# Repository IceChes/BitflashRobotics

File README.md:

# What is this project?
Bitflash Robotics is an attempt to modernize combat robotics electronics. 

## Devices (see devices page for more information)
### Firefly

ESP32C3-based BLE combat robot receiver. Connects to a standard BLE game controller and controls all other robotic components. Also runs more complex compute loads if needed.

Has 2 snap (serial) ports, 1 servo port, and 1 Qwiic port. 

### Impulse

megaAVR-based brushed motor controller. Connects to one of Firefly's snap ports using a standard Qwiic/Stemma QT cable. Controls 2 brushed motors with short circuit protection and supplies 3.3v power to the robot's low voltage subsystem. 

## Standards
### BFR Packet Protocol (See Bitflash Robotics Arduino Library page for more information)

High speed structured protocol for writing sets of bytes over a standard UART bus to communicate with components. Due to its efficiency, it is able to run at extremely high speeds. Has basic error checking procedures to ensure safety and reliability in high-noise, high-intensity environments.

### Snap Serial (See Snap Serial page for more information)

Snap Serial (or just Snap) is simply UART over a Qwiic/Stemma QT port. This helps reduce connector size in the extremely tight electronics bays inside of combat robots. 

## Robots
### ???

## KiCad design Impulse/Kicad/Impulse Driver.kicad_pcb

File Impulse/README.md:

# Impulse
A better combat robot motor driver.

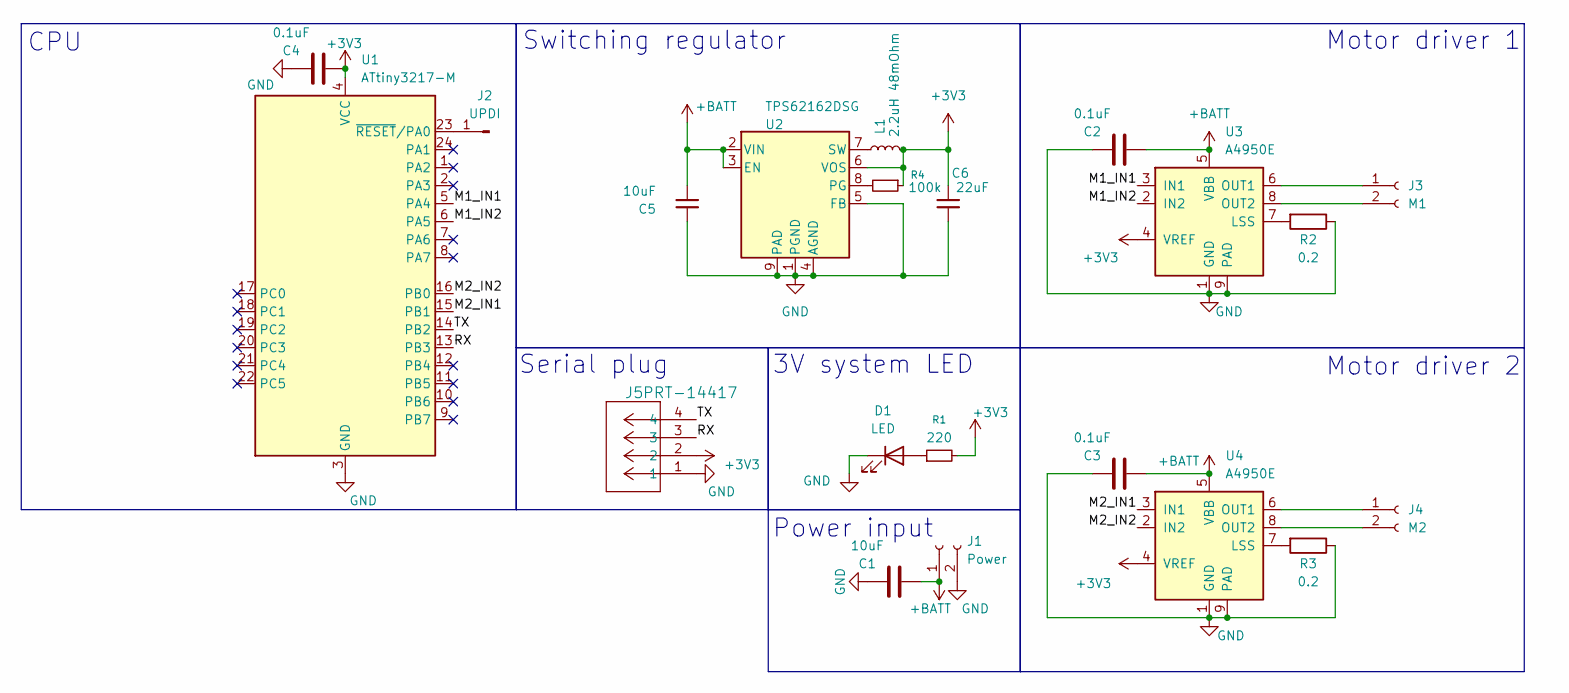
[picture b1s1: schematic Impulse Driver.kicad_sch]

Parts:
C1: 10uF; C_0805_2012Metric; LCSC C440198
C2, C3, C4: 0.1uF; C_0402_1005Metric; LCSC C14663
C5: 10uF; C_0805_2012Metric
C6: 22uF; C_0805_2012Metric
D1: LED; LED_0805_2012Metric; LCSC C965814
J1: Power; PinSocket_1x02_P2.54mm_Vertical
J2: UPDI; PinHeader_1x01_P2.54mm_Vertical
J3: M1; PinSocket_1x02_P2.54mm_Vertical
J4: M2; PinSocket_1x02_P2.54mm_Vertical
J5: PRT-14417; QWIIC_SNAPSERIAL
L1: 2.2uH 48mOhm; L_Pulse_PA4332
R1: 220; R_0402_1005Metric; LCSC C2909336
R2, R3: 0.2; R_0402_1005Metric; LCSC C7467478
R4: 100k; R_0402_1005Metric
U1: ATtiny3217-M; QFN-24-1EP_4x4mm_P0.5mm_EP2.6x2.6mm; LCSC C1340514
U2: TPS62162DSG; Texas_DSG0008A_WSON-8-1EP_2x2mm_P0.5mm_EP0.9x1.6mm_ThermalV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
U3, U4: A4950E; SOIC-8-1EP_3.9x4.9mm_P1.27mm_EP2.41x3.3mm; LCSC C82404

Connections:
+3V3: C4.1, C6.1, J5.2, L1.2, R1.2, R4.1, U1.4 (VCC), U2.6 (VOS), U3.4 (VREF), U4.4 (VREF)
+BATT: C1.1, C2.1, C3.1, C5.1, J1.1, U2.2 (VIN), U2.3 (EN), U3.5 (VBB), U4.5 (VBB)
/M1_IN1: U1.5 (PA4), U3.3 (IN1)
/M1_IN2: U1.6 (PA5), U3.2 (IN2)
/M2_IN1: U1.15 (PB1), U4.3 (IN1)
/M2_IN2: U1.16 (PB0), U4.2 (IN2)
/RX: J5.3, U1.13 (PB3)
/TX: J5.4, U1.14 (PB2)
GND: C1.2, C2.2, C3.2, C4.2, C5.2, C6.2, D1.1 (K), J1.2, J5.1, R2.1, R3.1, U1.3 (GND), U1.25 (GND), U2.1 (PGND), U2.4 (AGND), U2.5 (FB), U2.9 (PAD), U3.1 (GND), U3.9 (PAD), U4.1 (GND), U4.9 (PAD)
unnamed: D1.2 (A), R1.1
unnamed: J2.1 (Pin_1_1), U1.23 (~RESET/PA0)
unnamed: J3.1, U3.6 (OUT1)
unnamed: J3.2, U3.8 (OUT2)
unnamed: J4.1, U4.6 (OUT1)
unnamed: J4.2, U4.8 (OUT2)
unnamed: R4.2, U2.8 (PG)
unnamed: L1.1, U2.7 (SW)
unnamed: R2.2, U3.7 (LSS)
unnamed: R3.2, U4.7 (LSS)

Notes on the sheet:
Serial plug
Motor driver 2
CPU
Switching regulator
Power input
3V system LED
Motor driver 1

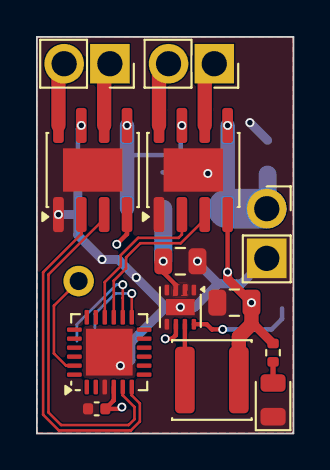
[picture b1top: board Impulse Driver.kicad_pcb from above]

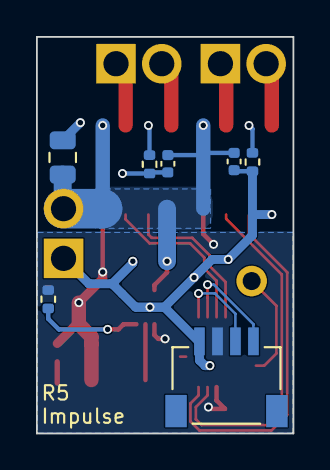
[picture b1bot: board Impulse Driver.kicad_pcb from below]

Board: 2 copper layers, 14.2 x 22.0 mm, 21 parts (7 on the bottom side), 19 nets.

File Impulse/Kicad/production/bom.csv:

Designator,Footprint,Quantity,Value,LCSC Part #
C1,0805,1,10uF,C440198
"C2, C3, C4",0402,3,0.1uF,C14663
C5,0805,1,10uF,
C6,0805,1,22uF,
D1,0805,1,LED,C965814
J1,PinSocket_1x02_P2.54mm_Vertical,1,Power,
J2,PinHeader_1x01_P2.54mm_Vertical,1,UPDI,
J5,QWIIC_SNAPSERIAL,1,PRT-14417,
L1,L_Pulse_PA4332,1,2.2uH 48mOhm,
R1,0402,1,220,C2909336
"R2, R3",0402,2,0.2,C7467478
R4,0402,1,100k,
U1,QFN-24-1EP_4x4mm_P0.5mm_EP2.6x2.6mm,1,ATtiny3217-M,C1340514
U2,Texas_DSG0008A_WSON-8-1EP_2x2mm_P0.5mm_EP0.9x1.6mm_ThermalVias,1,TPS62162DSG,
"U3, U4",SOIC-8-1EP_3.9x4.9mm_P1.27mm_EP2.41x3.3mm,2,A4950E,C82404

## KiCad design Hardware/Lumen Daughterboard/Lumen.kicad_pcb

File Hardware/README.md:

# Hardware
3D files and PCBs that aren't robots.

- JTAG2UPDI Carrier: A PCB where an Arduino Nano is used as a JTAG2UPDI programmer. Untested.
- Plastic Hub: A plastic version of a foam wheel hub for prototyping. Tested. Kinda works.
- SDMD: Atmega328P-based motor controller. Tested. Working.
- SnapSerial Driver: Attiny3217-based motor controller. Untested.
- Firefly Receiver: XIAO ESP32C3-based receiver. Untested.

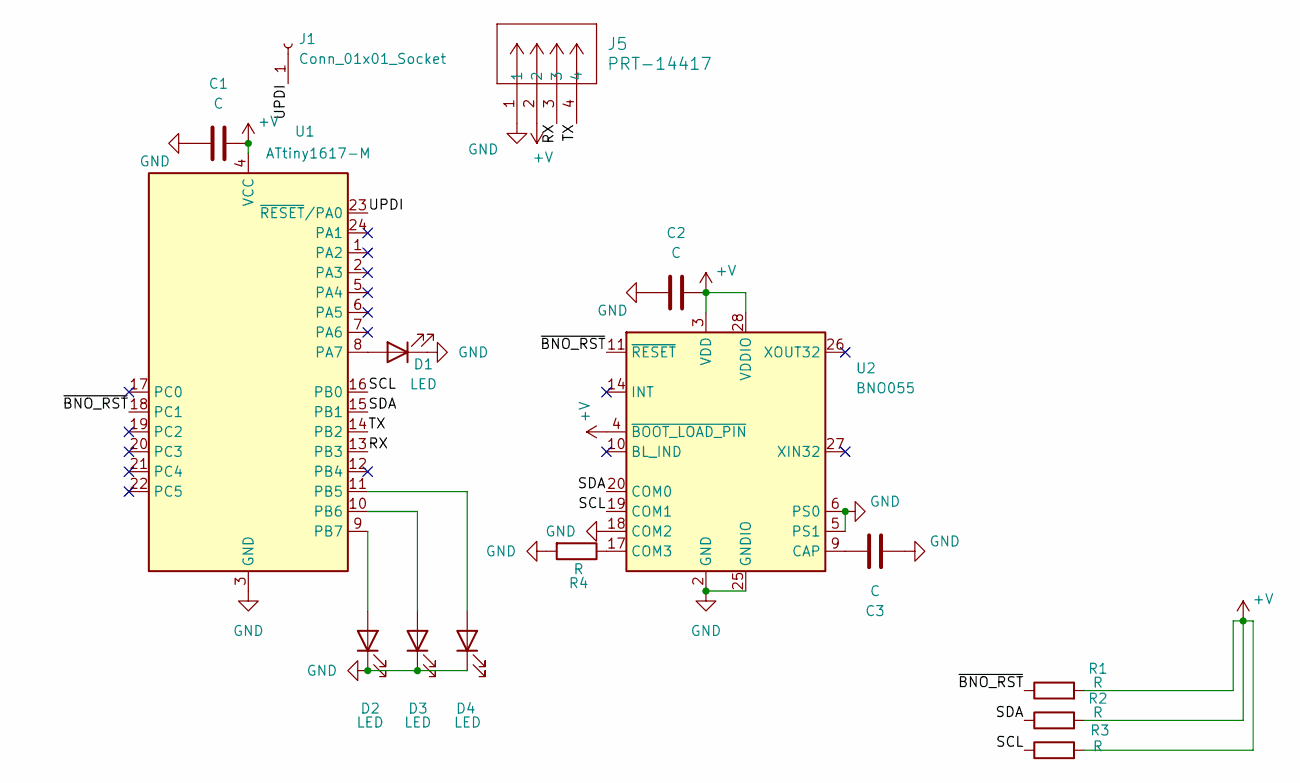
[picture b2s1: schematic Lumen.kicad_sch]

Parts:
C1, C2, C3: C; C_0402_1005Metric
D1, D2, D3, D4: LED; LED_0805_2012Metric
J1: Conn_01x01_Socket; PinSocket_1x01_P2.54mm_Vertical
J5: PRT-14417; QWIIC_SNAPSERIAL
R1, R2, R3, R4: R; R_0402_1005Metric
U1: ATtiny1617-M; QFN-24-1EP_4x4mm_P0.5mm_EP2.6x2.6mm
U2: BNO055; LGA-28_5.2x3.8mm_P0.5mm

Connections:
+V: C1.2, C2.2, J5.2, R1.2, R2.2, R3.2, U1.4 (VCC), U2.3 (VDD), U2.4 (~BOOT_LOAD_PIN), U2.28 (VDDIO)
/RX: J5.3, U1.13 (PB3)
/SCL: R3.1, U1.16 (PB0), U2.19 (COM1)
/SDA: R2.1, U1.15 (PB1), U2.20 (COM0)
/TX: J5.4, U1.14 (PB2)
/UPDI: J1.1, U1.23 (~RESET/PA0)
/~BNO_RST: R1.1, U1.18 (PC1), U2.11 (~RESET)
GND: C1.1, C2.1, C3.1, D1.1 (K), D2.1 (K), D3.1 (K), D4.1 (K), J5.1, R4.2, U1.3 (GND), U1.25 (GND), U2.2 (GND), U2.5 (PS1), U2.6 (PS0), U2.18 (COM2), U2.25 (GNDIO)
unnamed: D1.2 (A), U1.8 (PA7)
unnamed: D2.2 (A), U1.9 (PB7)
unnamed: D3.2 (A), U1.10 (PB6)
unnamed: D4.2 (A), U1.11 (PB5)
unnamed: C3.2, U2.9 (CAP)
unnamed: R4.1, U2.17 (COM3)

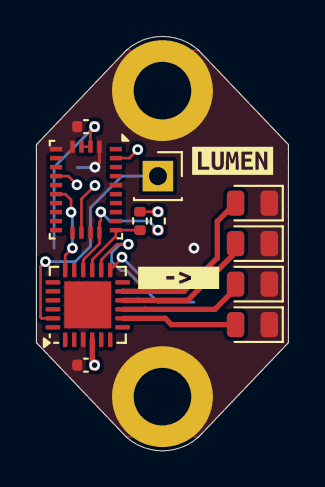
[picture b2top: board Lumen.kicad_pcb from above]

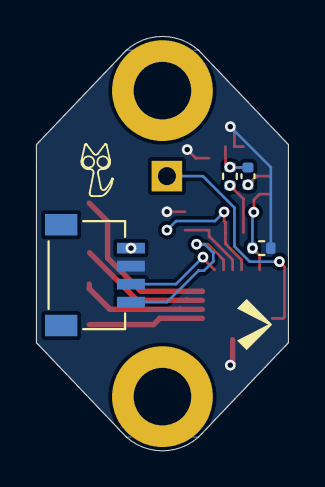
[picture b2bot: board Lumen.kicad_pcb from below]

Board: 2 copper layers, 14.0 x 23.0 mm, 17 parts (4 on the bottom side), 14 nets.

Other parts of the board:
kibuzzard-68C582FB: G***; kibuzzard-68C582FB
kibuzzard-68C58277: G***; kibuzzard-68C58277

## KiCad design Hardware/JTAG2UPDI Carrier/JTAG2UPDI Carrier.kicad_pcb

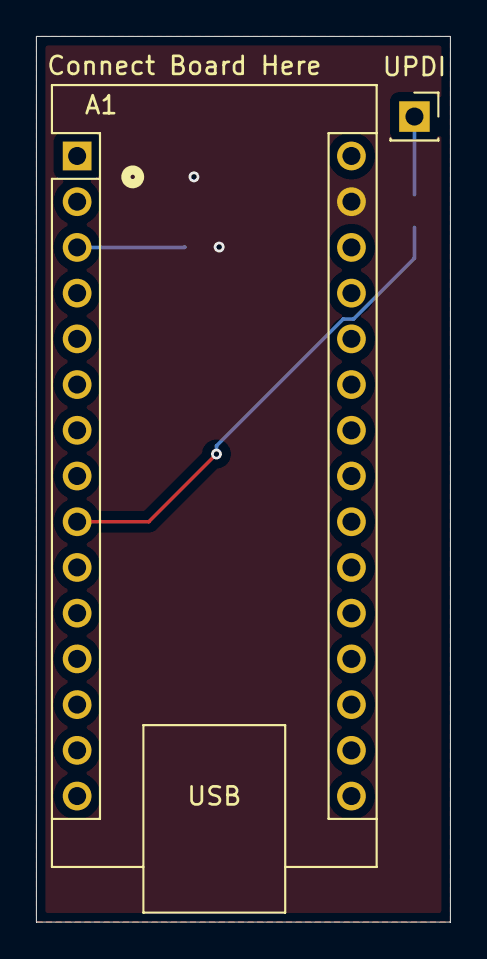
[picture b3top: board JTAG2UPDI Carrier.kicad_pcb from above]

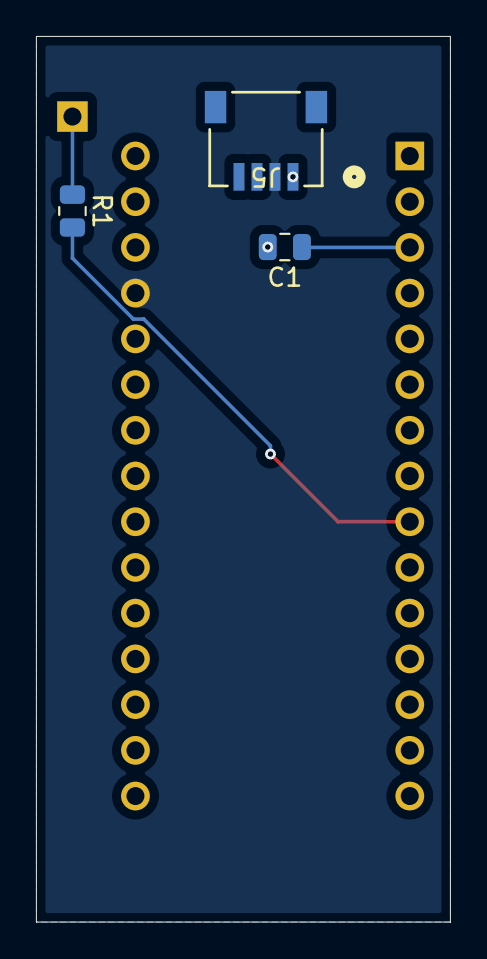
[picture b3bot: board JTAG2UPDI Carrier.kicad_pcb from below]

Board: 2 copper layers, 23.0 x 49.2 mm, 5 parts (3 on the bottom side), 5 nets.

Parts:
A1: Arduino_Nano_v3.x; Arduino_Nano
C1: C; C_0805_2012Metric
J5: PRT-14417; CONN_PRT-14417_SPK
R1: R; R_0805_2012Metric
UPDI: Conn_01x01_Socket; PinSocket_1x01_P2.54mm_Vertical

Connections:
+5V: A1.27 (+5V), J5.2
GND: A1.29 (GND), C1.2, J5.1
unnamed: A1.9 (D6), R1.2
unnamed: A1.3 (~RESET), C1.1
unnamed: R1.1, UPDI.1

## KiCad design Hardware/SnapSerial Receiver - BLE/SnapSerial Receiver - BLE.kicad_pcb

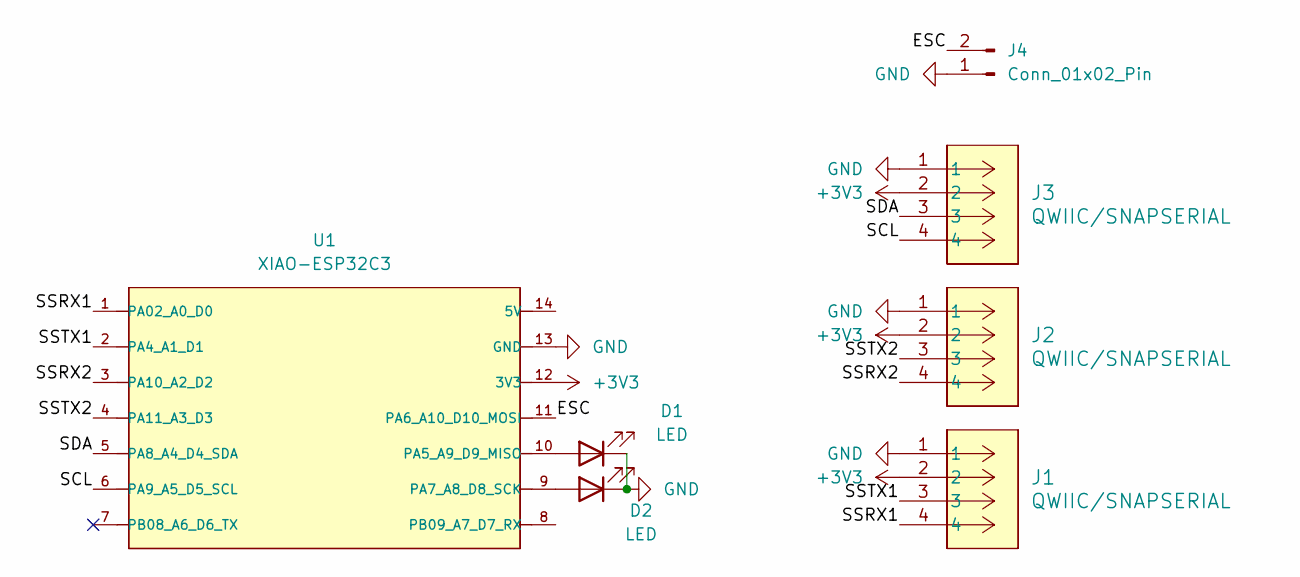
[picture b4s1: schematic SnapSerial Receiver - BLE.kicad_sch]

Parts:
D1, D2: LED; LED_0805_2012Metric
J1, J2, J3: QWIIC/SNAPSERIAL; QWIIC_SNAPSERIAL
J4: Conn_01x02_Pin; PinSocket_1x02_P2.54mm_Vertical
U1: XIAO-ESP32C3

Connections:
+3V3: J1.2, J2.2, J3.2, U1.12 (3V3)
/ESC: J4.2, U1.11 (PA6_A10_D10_MOSI)
/SCL: J3.4, U1.6 (PA9_A5_D5_SCL)
/SDA: J3.3, U1.5 (PA8_A4_D4_SDA)
/SSRX1: J1.4, U1.1 (PA02_A0_D0)
/SSRX2: J2.4, U1.3 (PA10_A2_D2)
/SSTX1: J1.3, U1.2 (PA4_A1_D1)
/SSTX2: J2.3, U1.4 (PA11_A3_D3)
GND: D1.1 (K), D2.1 (K), J1.1, J2.1, J3.1, J4.1, U1.13 (GND)
unnamed: D1.2 (A), U1.10 (PA5_A9_D9_MISO)
unnamed: D2.2 (A), U1.9 (PA7_A8_D8_SCK)

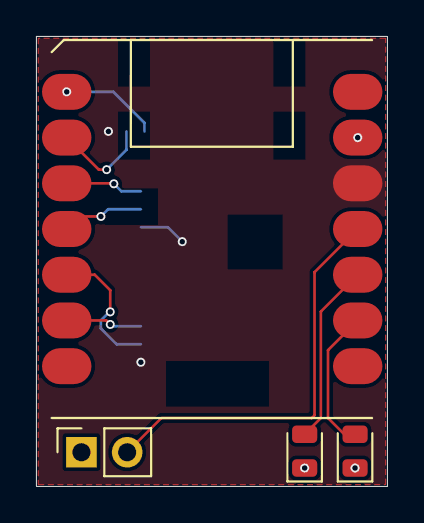
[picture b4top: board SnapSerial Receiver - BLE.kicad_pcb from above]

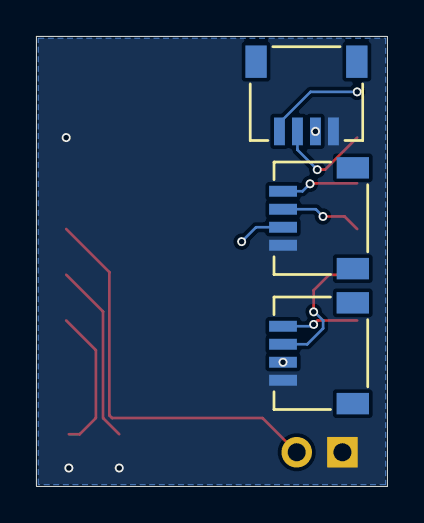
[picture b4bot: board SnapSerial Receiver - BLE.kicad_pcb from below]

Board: 2 copper layers, 19.5 x 25.0 mm, 7 parts (3 on the bottom side), 11 nets.

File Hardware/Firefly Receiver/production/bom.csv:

Designator,Footprint,Quantity,Value,LCSC Part #
"D1, D2",0805,2,LED,
"J1, J2, J3",QWIIC_SNAPSERIAL,3,QWIIC/SNAPSERIAL,
J4,PinSocket_1x02_P2.54mm_Vertical,1,Conn_01x02_Pin,
U1,XIAO-ESP32C3,1,XIAO-ESP32C3,

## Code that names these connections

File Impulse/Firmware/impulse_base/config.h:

//motor controller pins
#define PIN_CHANNEL_1_A PIN_PA4
#define PIN_CHANNEL_1_B PIN_PA5
#define PIN_CHANNEL_2_A PIN_PB0
#define PIN_CHANNEL_2_B PIN_PB1



//user settings
#define USR_MOTOR_1_MAXIMUM_SPEED 255
#define USR_MOTOR_2_MAXIMUM_SPEED 255

//serial safety timeout
#define USR_SERIAL_SAFETY_TIMEOUT 10000

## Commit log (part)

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2025-08-28 new repo!
2025-09-04 yes
    - Add provisions to get controller parameters in the bot fw
    - Modify SDMD firmware to work with the new snapserial driver but idk if it will work because the pcb isn't here yet
2025-09-08 moved file
2025-09-10 work in progress moving stuff
2025-09-10 move stuff
2025-09-11 Create Lumen and modify MF
2025-09-12 Update Lumen
2025-09-12 Lumen :D
2025-09-19 Flesh out snapdriver and other stuff
2025-09-19 More updates
